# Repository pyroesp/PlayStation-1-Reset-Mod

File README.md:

# PlayStation 1 Reset Mod  

PlayStation 1 controller combination reset mod.  
This mod when installed, allows you to reset your PlayStation through a button combination on the controller port 1.  

**Checkout the Wiki for more information.**

Disclaimer
----------  
Anyone contributing to this mod is in no way responsible to whatever happens to your PlayStation 1 after installing or removing it.  
You do this at your own risk.  
If you don't know what you're doing, go to someone that does.   

Do **NOT** reset whilst you're saving data. If you do, you'll most likely corrupt your game save and/or your memory card.  
You have been warned.    

Why
-------
Because I have a PSIO from Cybdyn System and there's no way to change games or get back into the PSIO menu system without resetting the PlayStation.  

Versions
--------

* V1.2: Added support for the xStation reset (long reset pulse)  
* V1.1: Fixed incorrect I/O  
* V1.0: First release  

How does it work
----------------
The PlayStation sends commands to the controller and the controller responds with the status of the buttons and joysticks.  
The command and data is read by the microcontroller and after some checks to see if the button combo has been pressed, it will reset the PlayStation.  
The communication is almost exactly like SPI, which is why I'm using it in the later versions of the mod.  

The button combination for the controllers is:  
- L2 + R2 + SELECT + START, for a short reset pulse  
- L2 + R2 + SELECT + CROSS, for a long reset pulse, since V1.2  

The lightgun combination is:
- A + B + TRIGGER, for a long reset pulse 

\***Note:** My mod is connected to controller port 1, but it can be adapted to also work with port 2.  

Tests
----- 
I have successfully tested this with a digital controller, a GUNCON and an analog controller.  

Schematic and PCB
-----------------

PCB is 14.5mm x 12mm, see images below.  

You can choose from three different cap sizes: 1206, 0805 and 0603.

Parts list
----------
Only two components needed for this mod: the microcontroller and **one** capacitor.  
\***Note:** Digikey links are for reference. Go to your electronics supplier of choice.  
1x [16F18325; 14-SOIC package](https://www.digikey.be/product-detail/en/microchip-technology/PIC16F18325-I-SL/PIC16F18325-I-SL-ND/5323625)  
1x [0.1µF 16V; 1206](https://www.digikey.be/product-detail/en/w-rth-elektronik/885012208030/732-8097-1-ND/5454724) **or** [0.1µF 16V; 0805](https://www.digikey.be/product-detail/en/w-rth-elektronik/885012207045/732-8045-1-ND/5454672) **or** [0.1µF 16V; 0603](https://www.digikey.be/product-detail/en/samsung-electro-mechanics/CL10B104KO8NNNC/1276-1005-1-ND/3889091) package  

\***Note:** Capacitor smd sizes:
* 1206 = 0.125 in × 0.06 in | 3.2 mm × 1.6 mm  
* 0805 = 0.080 in × 0.05 in | 2.0 mm × 1.25 mm
* 0603 = 0.060 in × 0.03 in | 1.6 mm × 0.8 mm

If you don't have a lot of experience soldering I recommend going for the 1206.

Youtube
-------
Proof of concept of the first version: https://www.youtube.com/watch?v=H-n-7R_S09U  
Final proof of concept of the first version: https://www.youtube.com/watch?v=lb_uCGyv6pY  

See also [an 8 part video playlist](https://www.youtube.com/playlist?list=PLGaX4WJGgdHiliTw9mCHme-9vNLV6fG6E) where I go from the Arduino Nano to a PIC16F18325 and a schematic with PCB.  

Three controllers programmed  
----------------------------
Digital, Analog and GUNCON controllers have been programmed.  

/* Controller ID */  
#define ID_DIG_CTRL 0x5A41 // digital  
#define ID_ANP_CTRL 0x5A73 // analog/pad  
#define ID_ANS_CTRL 0x5A53 // analog/stick  
#define ID_GUNCON_CTRL 0x5A63 // light gun  

License
-------
Attribution-ShareAlike 4.0 International, see license file for more info

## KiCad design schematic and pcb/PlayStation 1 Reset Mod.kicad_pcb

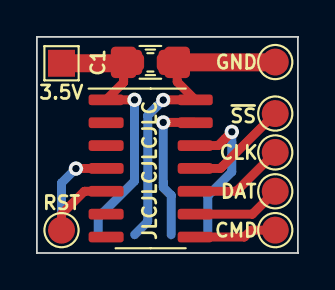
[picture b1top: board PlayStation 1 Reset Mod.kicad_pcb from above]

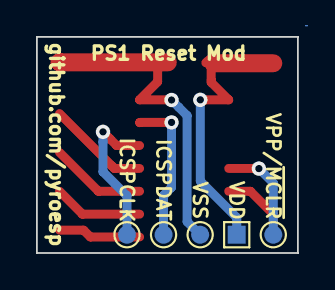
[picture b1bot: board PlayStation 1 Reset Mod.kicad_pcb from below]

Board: 2 copper layers, 14.5 x 12.0 mm, 15 parts (5 on the bottom side), 9 nets.

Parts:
3.5V: TestPoint; TestPoint_Pad_1.5x1.5mm
C1: 0.1uF; C_1206_3216Metric_Pad1.42x1.75mm_HandSolder
C2: 0.1uF; C_0805_2012Metric_Pad1.15x1.40mm_HandSolder
C3: 0.1uF; C_0603_1608Metric_Pad1.05x0.95mm_HandSolder
CLK: TestPoint; TestPoint_Pad_D1.5mm
CMD: TestPoint; TestPoint_Pad_D1.5mm
DAT: TestPoint; TestPoint_Pad_D1.5mm
GND: TestPoint; TestPoint_Pad_D1.5mm
ICSPCLK: TestPoint; TestPoint_Pad_D1.0mm
ICSPDAT: TestPoint; TestPoint_Pad_D1.0mm
RST: TestPoint; TestPoint_Pad_D1.5mm
U1: PIC16F18325-ISL; SOIC-14_3.9x8.7mm_P1.27mm
VDD: TestPoint; TestPoint_Pad_1.0x1.0mm
VPP/~MCLR: TestPoint; TestPoint_Pad_D1.0mm
VSS: TestPoint; TestPoint_Pad_D1.0mm

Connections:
+3V3: 3.5V.1, C1.1, C2.1, C3.1, U1.1, VDD.1
/CLK: CLK.1, U1.10
/CMD: CMD.1, U1.8
/DATA: DAT.1, U1.9
/ICSPCLK: ICSPCLK.1, U1.12
/ICSPDAT: ICSPDAT.1, U1.13
/RESET: RST.1, U1.5
/VPP\~MCLR: U1.4, VPP/~MCLR.1
GND: C1.2, C2.2, C3.2, GND.1, U1.14, VSS.1

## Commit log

2019-06-19 first commit main program
2019-06-20 updated code
    some data missing during read, so now it will read until the slave select pin is high (stop transmission) and only then process the read data
2019-06-22 updated code, no interrupt used, only polling
    Using spi interrupt I could only read either data or cmd, but not both. So I tried using external pin interrupt on the clock to read both CMD and DATA, but for some reason I couldn't get it to synch 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
    Because of that some input status were lost and I couldn't get CMD and DATA to be reliable.
    Now I'm using polling and it seems to work fine, although using a GUNCON doesn't yet work...
2019-06-23 updated code, fixed guncon, fixed reset loop bug
    Found the issue with the guncon, it was a missing break in the switch...
    Also found a reset loop bug when you disconnect the controller from the PS1 after resetting it. The old data was never cleared so the arduino thought it receives a reset command and resets the PS1.
2019-06-23 removed POC from comment, not POC anymore
2019-07-07 added pictures of the mod
2019-07-07 deleted
2019-07-07 added box around parallel port reset pin 2
2019-07-07 added debug ifdef here and there for the serial print stuff
2019-10-15 update with all codes and schematic + pcb
    this update contains all files and schematic + pcb I worked on whilst streaming
2019-10-15 move pictures around
2019-10-15 renamed folder to pictures
2019-10-15 wrong code and flowchart, added correct code
2019-10-15 minor update
2019-10-15 fix arduino ide error
    renamed file and folder without spaces because arduino ide couldn't open the file
2019-10-15 minor update readme
2019-10-18 Delete playstation_controller.ino
    this one is the arduino nano polling code
2019-10-19 updated schematic and PCB
    fix issues #1, #2, #3, #5
2019-10-19 add pictures of schematic and pcb
2019-10-19 remove spi folder for the 328pb
2019-10-19 specify jlc order number location
    this fixes issue #8
2019-10-19 added 0603 capacitor
    I've added an extra 0603 capacitor footprint
2019-10-19 minor addition to schematic
    added rectangle around the 3 caps on the schematic with text indicating to only install one
2019-10-19 gerber files update
2019-10-20 added part lists to readme
2019-10-20 fix code for first release
    issue #9
2019-10-20 update of the readme
    added a caution title
2019-10-27 add jlcpcb parameters
2019-10-27 fixed typo
2019-10-27 add correct flowchart
2019-10-27 add flowchart images
2019-11-30 added guide pictures
    provided by Damn-Deal-Done from ConsolesUnleashed.com
2019-12-14 switched data and cmd in code, compared to actual hardware pcb
    * Seems like SPI1 and SPI2 were switched on the hardware - fixed in code.
    * I also added the analog pad define back, because that's the one I actually have.
2019-12-26 updated guide images
2020-02-13 Update main.c
    added 5A79 ID for compatibility with Playstation 2
2020-11-27 gitignore for kicad stuff
2020-11-27 general update
2020-11-30 updated code for release V1.2
2020-11-30 updated readme for release V1.2
2020-11-30 add 555 timer circuit for HW support of the xStation
2020-11-30 added and moved pictures for the 555 timer circuit
2020-12-21 moved arduino stuff into old folder
2020-12-21 added PU23 guide
2020-12-21 removed atmega folders
2024-07-20 add sony part number to controller IDs
